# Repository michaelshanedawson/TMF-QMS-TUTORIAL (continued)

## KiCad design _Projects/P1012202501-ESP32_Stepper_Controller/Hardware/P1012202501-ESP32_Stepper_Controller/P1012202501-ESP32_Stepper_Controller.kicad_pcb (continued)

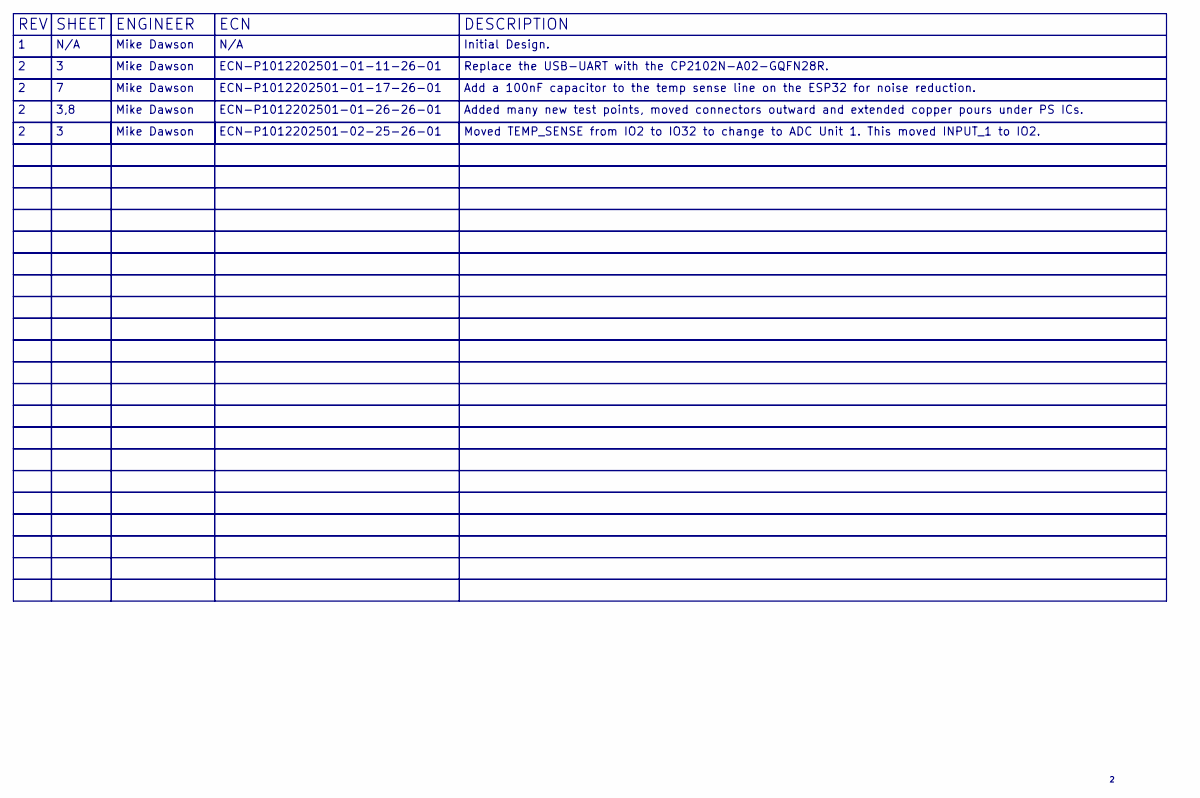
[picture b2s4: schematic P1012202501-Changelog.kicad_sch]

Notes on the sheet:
ECN
ECN-P1012202501-01-11-26-01
SHEET
DESCRIPTION
ECN-P1012202501-02-25-26-01
3,8
Mike Dawson
ECN-P1012202501-01-26-26-01
ECN-P1012202501-01-17-26-01
N/A
Replace the USB-UART with the CP2102N-A02-GQFN28R.
Initial Design.
REV
ENGINEER
Add a 100nF capacitor to the temp sense line on the ESP32 for noise reduction.
Added many new test points, moved connectors outward and extended copper pours under PS ICs.
Moved TEMP_SENSE from IO2 to IO32 to change to ADC Unit 1. This moved INPUT_1 to IO2.

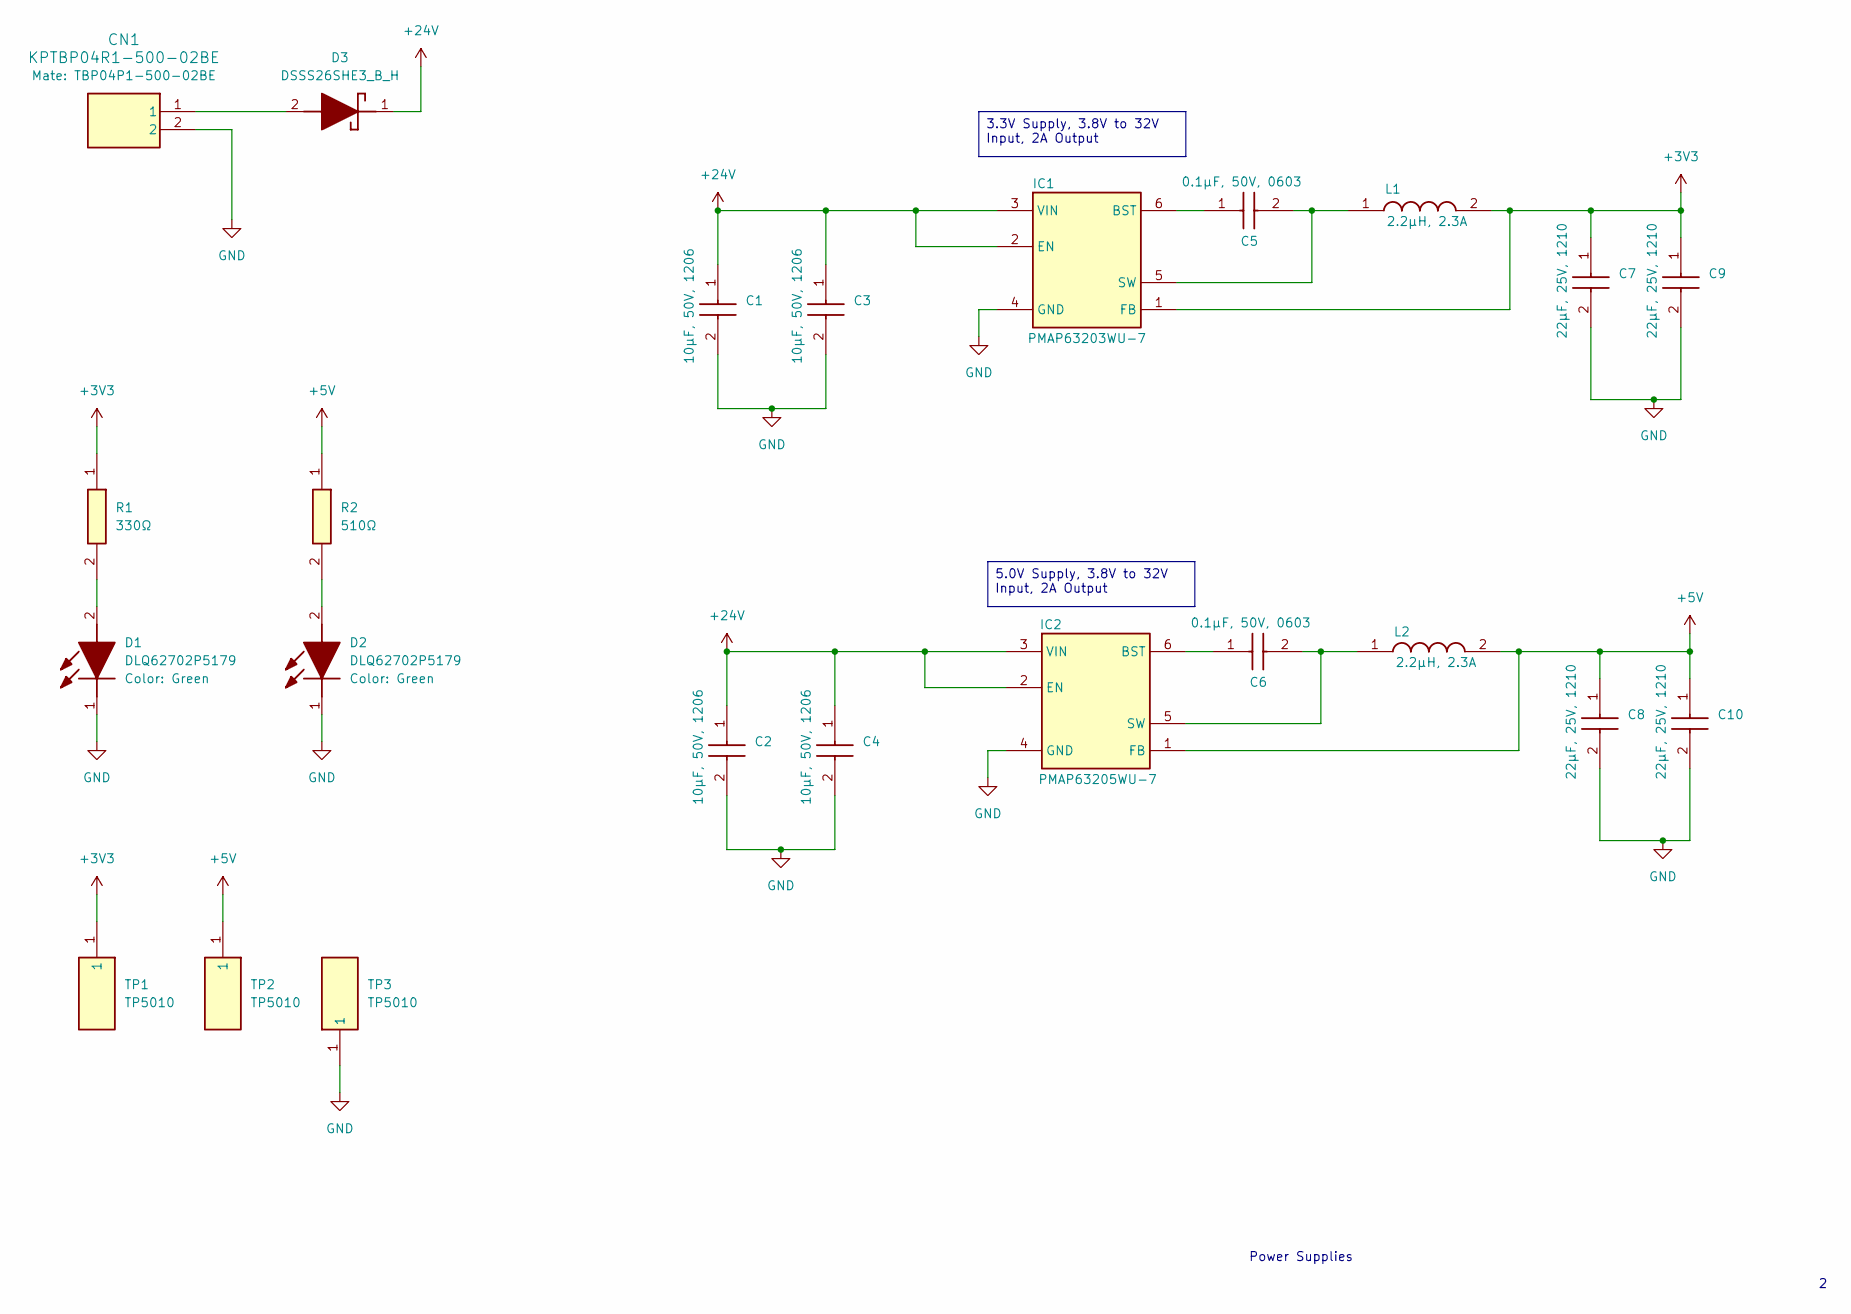
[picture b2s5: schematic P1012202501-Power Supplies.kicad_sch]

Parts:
C1, C2, C3, C4: CC1206106050AAAX7R; CAP-1206
C5, C6: CC0603104050AAAX7R; CAP-0603
C7, C8, C9, C10: CC1210226025AAAX7R; CAP-1210
CN1: KPTBP04R1-500-02BE; TBP04R1-500-02BE
D1, D2: DLQ62702P5179; LED-0805
D3: DSSS26SHE3_B_H; SMA
IC1: PMAP63203WU-7; TSOT-26-6
IC2: PMAP63205WU-7; TSOT-26-6
L1, L2: LSRP2512-2R2M; IND-1005
R1: RC0603330075AAA; RES-0603
R2: RC0603510075AAA; RES-0603
TP1, TP2, TP3: TP5010; 5010

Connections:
+3V3: C7.1, C9.1, IC1.1 (FB), L1.2, R1.1, TP1.1; also elsewhere on the board
+5V: C8.1, C10.1, IC2.1 (FB), L2.2, R2.1, TP2.1; also elsewhere on the board
+24V: C1.1, C2.1, C3.1, C4.1, D3.1 (K), IC1.2 (EN), IC1.3 (VIN), IC2.2 (EN), IC2.3 (VIN); also elsewhere on the board
GND: C1.2, C2.2, C3.2, C4.2, C7.2, C8.2, C9.2, C10.2, CN1.2, D1.1 (K), D2.1 (K), IC1.4 (GND), IC2.4 (GND), TP3.1; also elsewhere on the board
unnamed: D1.2 (A), R1.2
unnamed: D2.2 (A), R2.2
unnamed: CN1.1, D3.2 (A)
unnamed: C5.1, IC1.6 (BST)
unnamed: C5.2, IC1.5 (SW), L1.1
unnamed: C6.1, IC2.6 (BST)
unnamed: C6.2, IC2.5 (SW), L2.1

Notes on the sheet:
Power Supplies
3.3V Supply, 3.8V to 32V Input, 2A Output
5.0V Supply, 3.8V to 32V Input, 2A Output

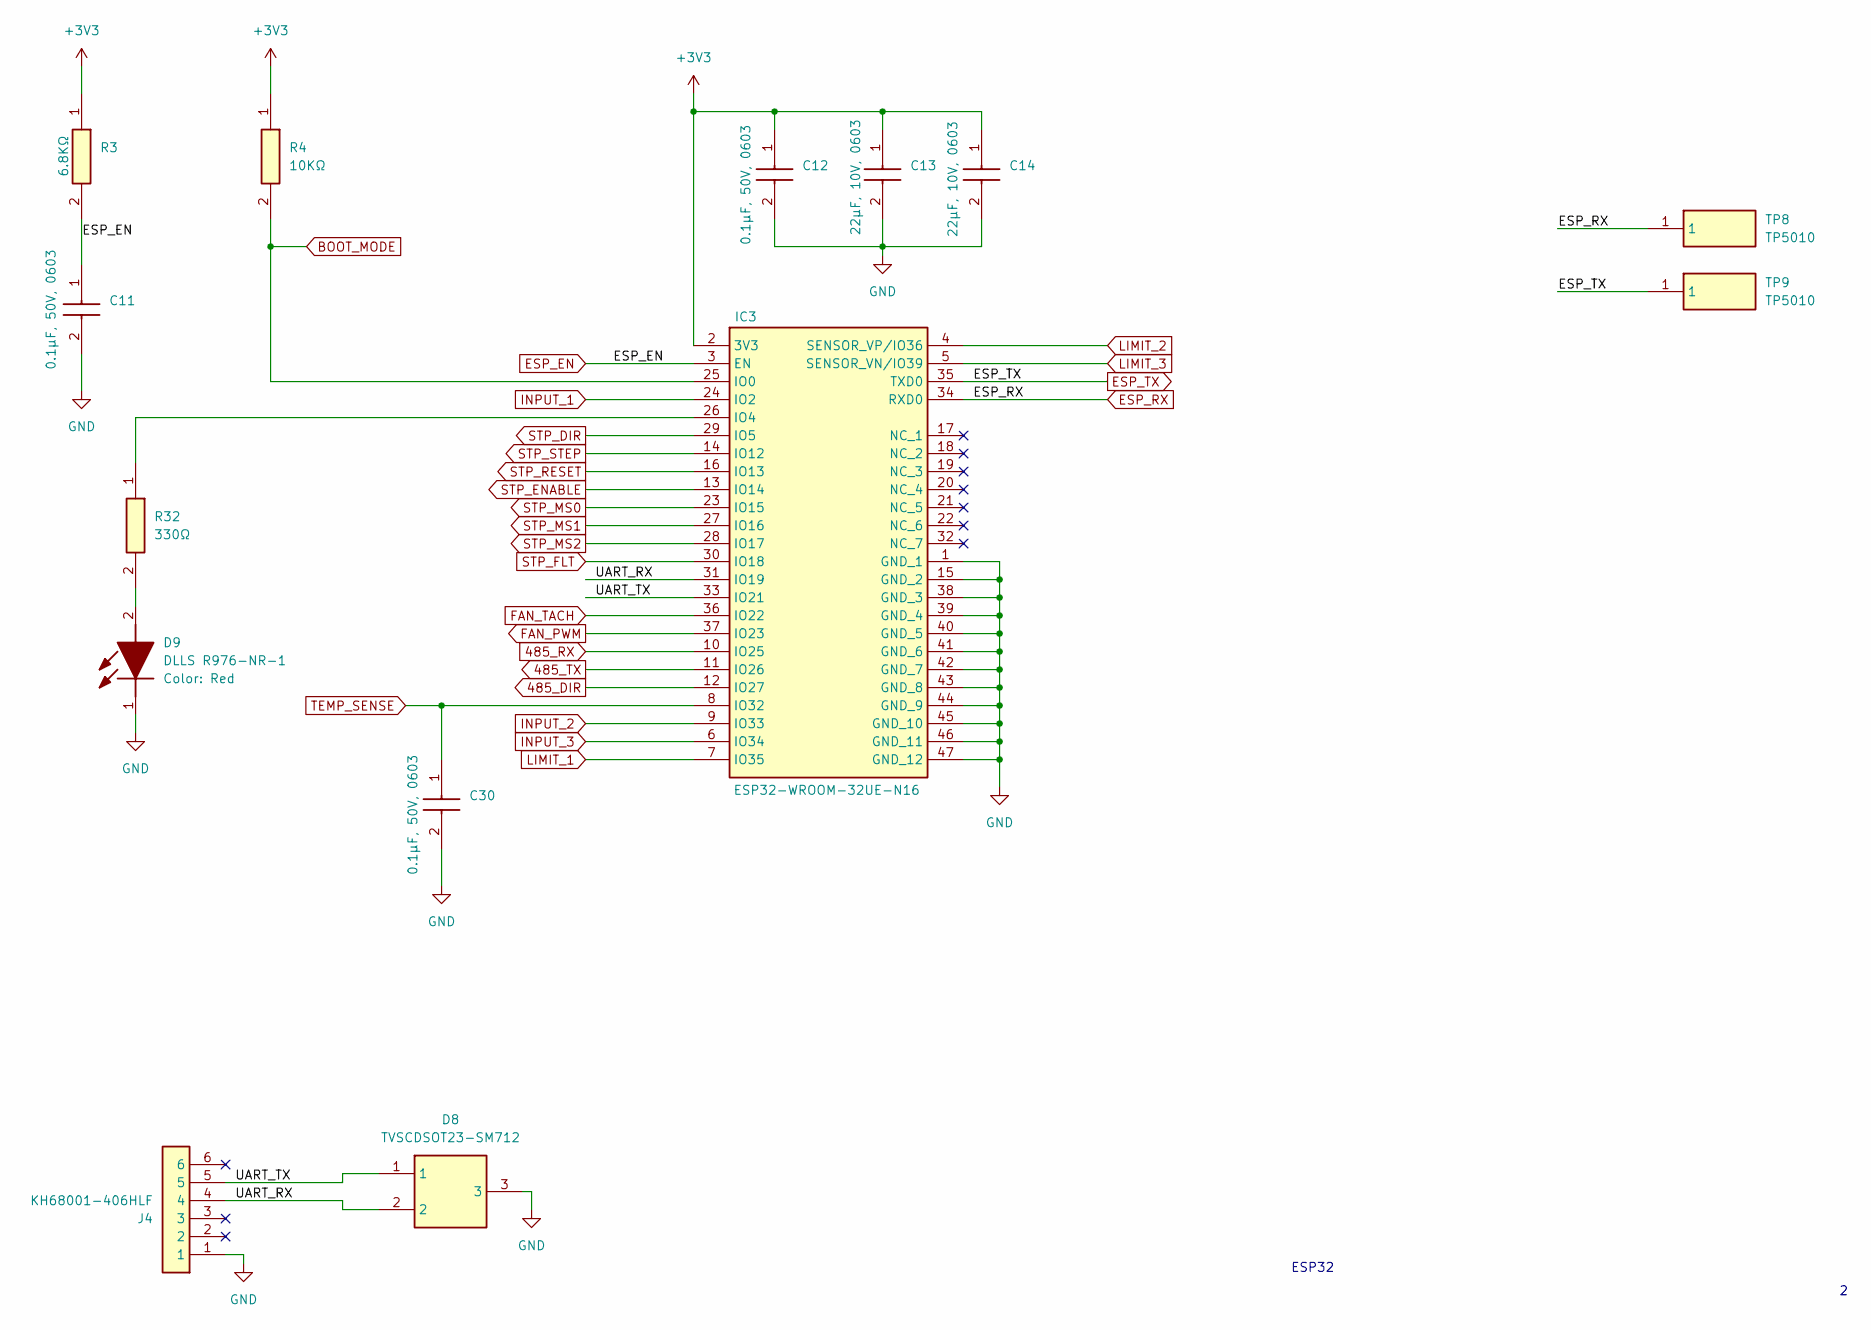
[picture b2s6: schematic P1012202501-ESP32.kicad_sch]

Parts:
C11, C12, C30: CC0603104050AAAX7R; CAP-0603
C13, C14: CC0603226010AABX5R; CAP-0603
D8: TVSCDSOT23-SM712; SOT-23-3
D9: DLLS R976-NR-1; LED-0805
IC3: ESP32-WROOM-32UE-N16; ESP32WROOM32UE
J4: KH68001-406HLF; 6x1HDR2.54mm
R3: RC0603682075AAA; RES-0603
R4: RC060310K2075AAA; RES-0603
R32: RC0603330075AAA; RES-0603
TP8, TP9: TP5010; 5010

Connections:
485_DIR: IC3.12 (IO27); also elsewhere on the board
485_RX: IC3.10 (IO25); also elsewhere on the board
485_TX: IC3.11 (IO26); also elsewhere on the board
+3V3: C12.1, C13.1, C14.1, IC3.2 (3V3), R3.1, R4.1; also elsewhere on the board
/ESP32/UART_RX: D8.2, IC3.31 (IO19), J4.4
/ESP32/UART_TX: D8.1, IC3.33 (IO21), J4.5
BOOT_MODE: IC3.25 (IO0), R4.2; also elsewhere on the board
ESP_EN: C11.1, IC3.3 (EN), R3.2; also elsewhere on the board
ESP_RX: IC3.34 (RXD0), TP8.1; also elsewhere on the board
ESP_TX: IC3.35 (TXD0), TP9.1; also elsewhere on the board
FAN_PWM: IC3.37 (IO23); also elsewhere on the board
FAN_TACH: IC3.36 (IO22); also elsewhere on the board
GND: C11.2, C12.2, C13.2, C14.2, C30.2, D8.3, D9.1 (K), IC3.1 (GND_1), IC3.15 (GND_2), IC3.38 (GND_3), IC3.39 (GND_4), IC3.40 (GND_5), IC3.41 (GND_6), IC3.42 (GND_7), IC3.43 (GND_8), IC3.44 (GND_9), IC3.45 (GND_10), IC3.46 (GND_11), IC3.47 (GND_12), J4.1; also elsewhere on the board
INPUT_1: IC3.24 (IO2); also elsewhere on the board
INPUT_2: IC3.9 (IO33); also elsewhere on the board
INPUT_3: IC3.6 (IO34); also elsewhere on the board
LIMIT_1: IC3.7 (IO35); also elsewhere on the board
LIMIT_2: IC3.4 (SENSOR_VP/IO36); also elsewhere on the board
LIMIT_3: IC3.5 (SENSOR_VN/IO39); also elsewhere on the board
unnamed: D9.2 (A), R32.2
unnamed: IC3.26 (IO4), R32.1
STP_DIR: IC3.29 (IO5); also elsewhere on the board
STP_ENABLE: IC3.13 (IO14); also elsewhere on the board
STP_FLT: IC3.30 (IO18); also elsewhere on the board
STP_MS0: IC3.23 (IO15); also elsewhere on the board
STP_MS1: IC3.27 (IO16); also elsewhere on the board
STP_MS2: IC3.28 (IO17); also elsewhere on the board
STP_RESET: IC3.16 (IO13); also elsewhere on the board
STP_STEP: IC3.14 (IO12); also elsewhere on the board
TEMP_SENSE: C30.1, IC3.8 (IO32); also elsewhere on the board

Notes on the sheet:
ESP32

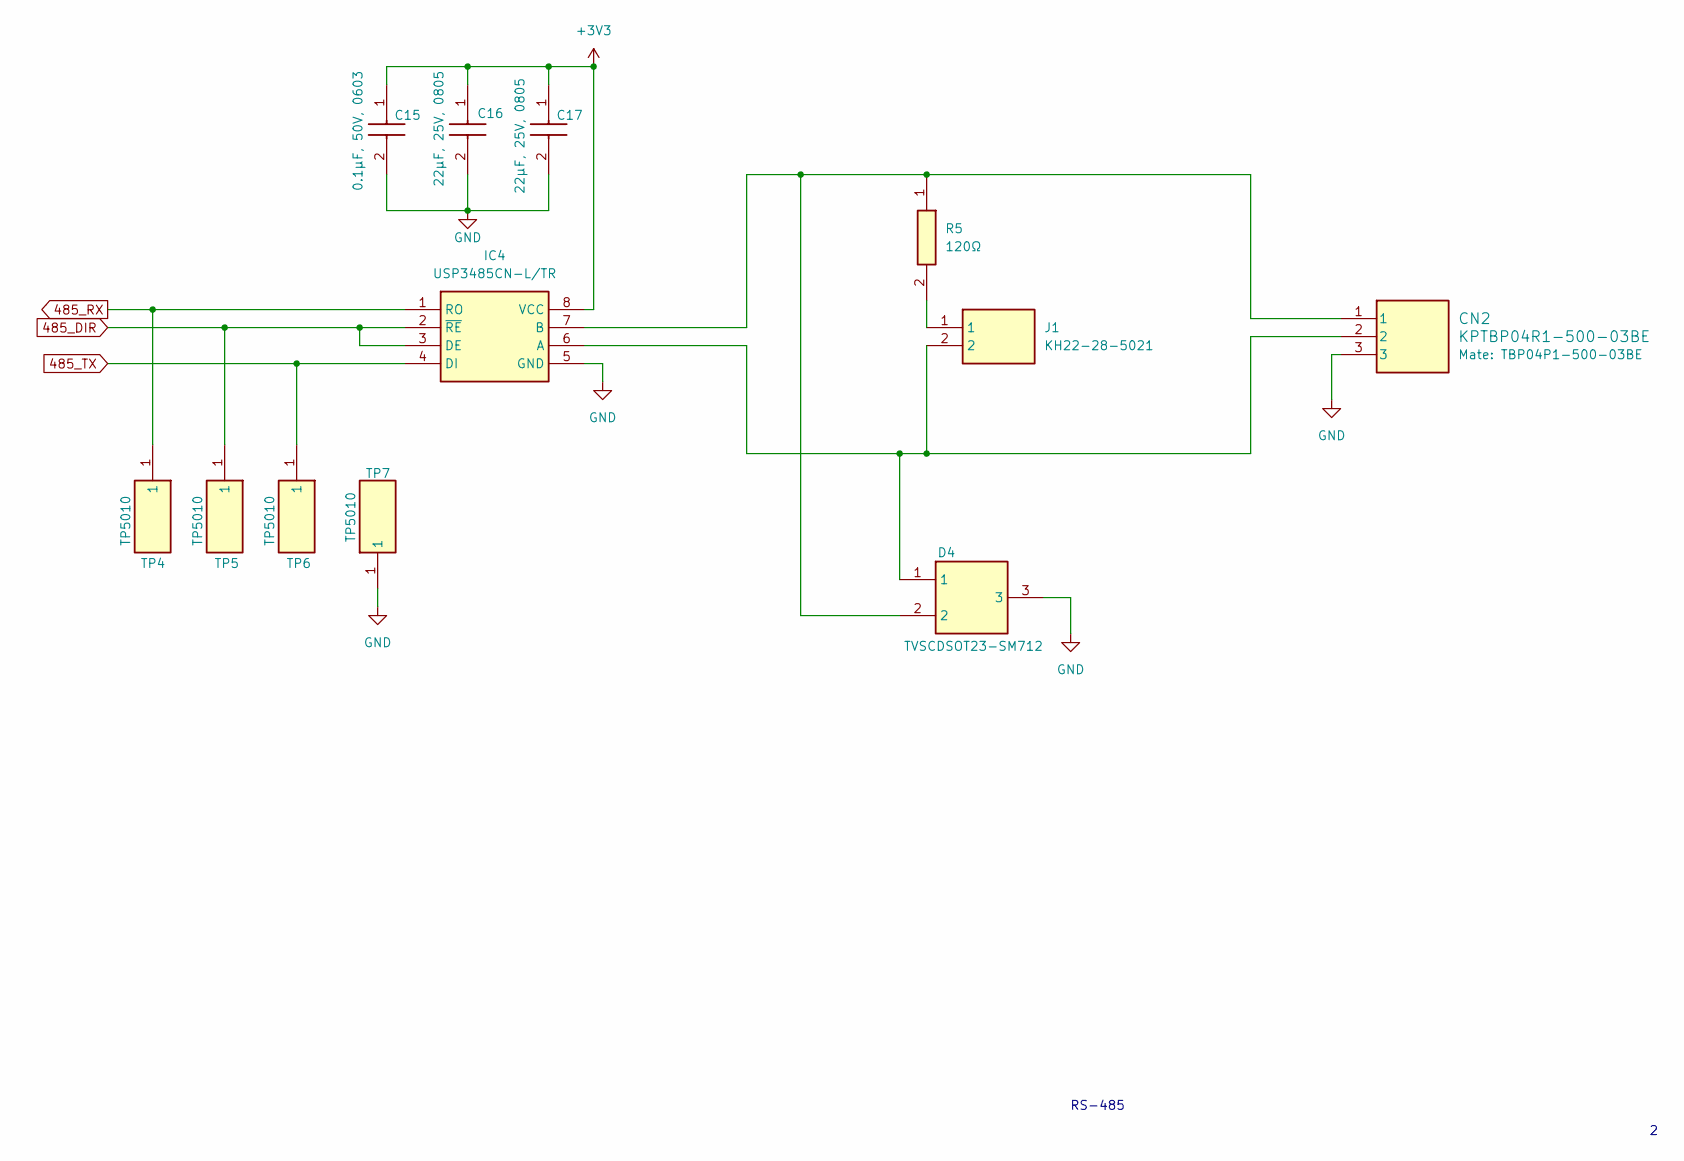
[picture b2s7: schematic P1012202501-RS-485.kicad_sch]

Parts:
C15: CC0603104050AAAX7R; CAP-0603
C16, C17: CC0805226025AABX5R; CAP-0805
CN2: KPTBP04R1-500-03BE; TBP04R1-500-03BE
D4: TVSCDSOT23-SM712; SOT-23-3
IC4: USP3485CN-L/TR; SOIC-8
J1: KH22-28-5021; 2x1HDR2.54mm
R5: RC0805121150AAB; RES-0805
TP4, TP5, TP6, TP7: TP5010; 5010

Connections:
485_DIR: IC4.2 (~RE), IC4.3 (DE), TP5.1; also elsewhere on the board
485_RX: IC4.1 (RO), TP4.1; also elsewhere on the board
485_TX: IC4.4 (DI), TP6.1; also elsewhere on the board
+3V3: C15.1, C16.1, C17.1, IC4.8 (VCC); also elsewhere on the board
GND: C15.2, C16.2, C17.2, CN2.3, D4.3, IC4.5 (GND), TP7.1; also elsewhere on the board
unnamed: CN2.2, D4.1, IC4.6 (A), J1.2
unnamed: CN2.1, D4.2, IC4.7 (B), R5.1
unnamed: J1.1, R5.2

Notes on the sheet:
RS-485

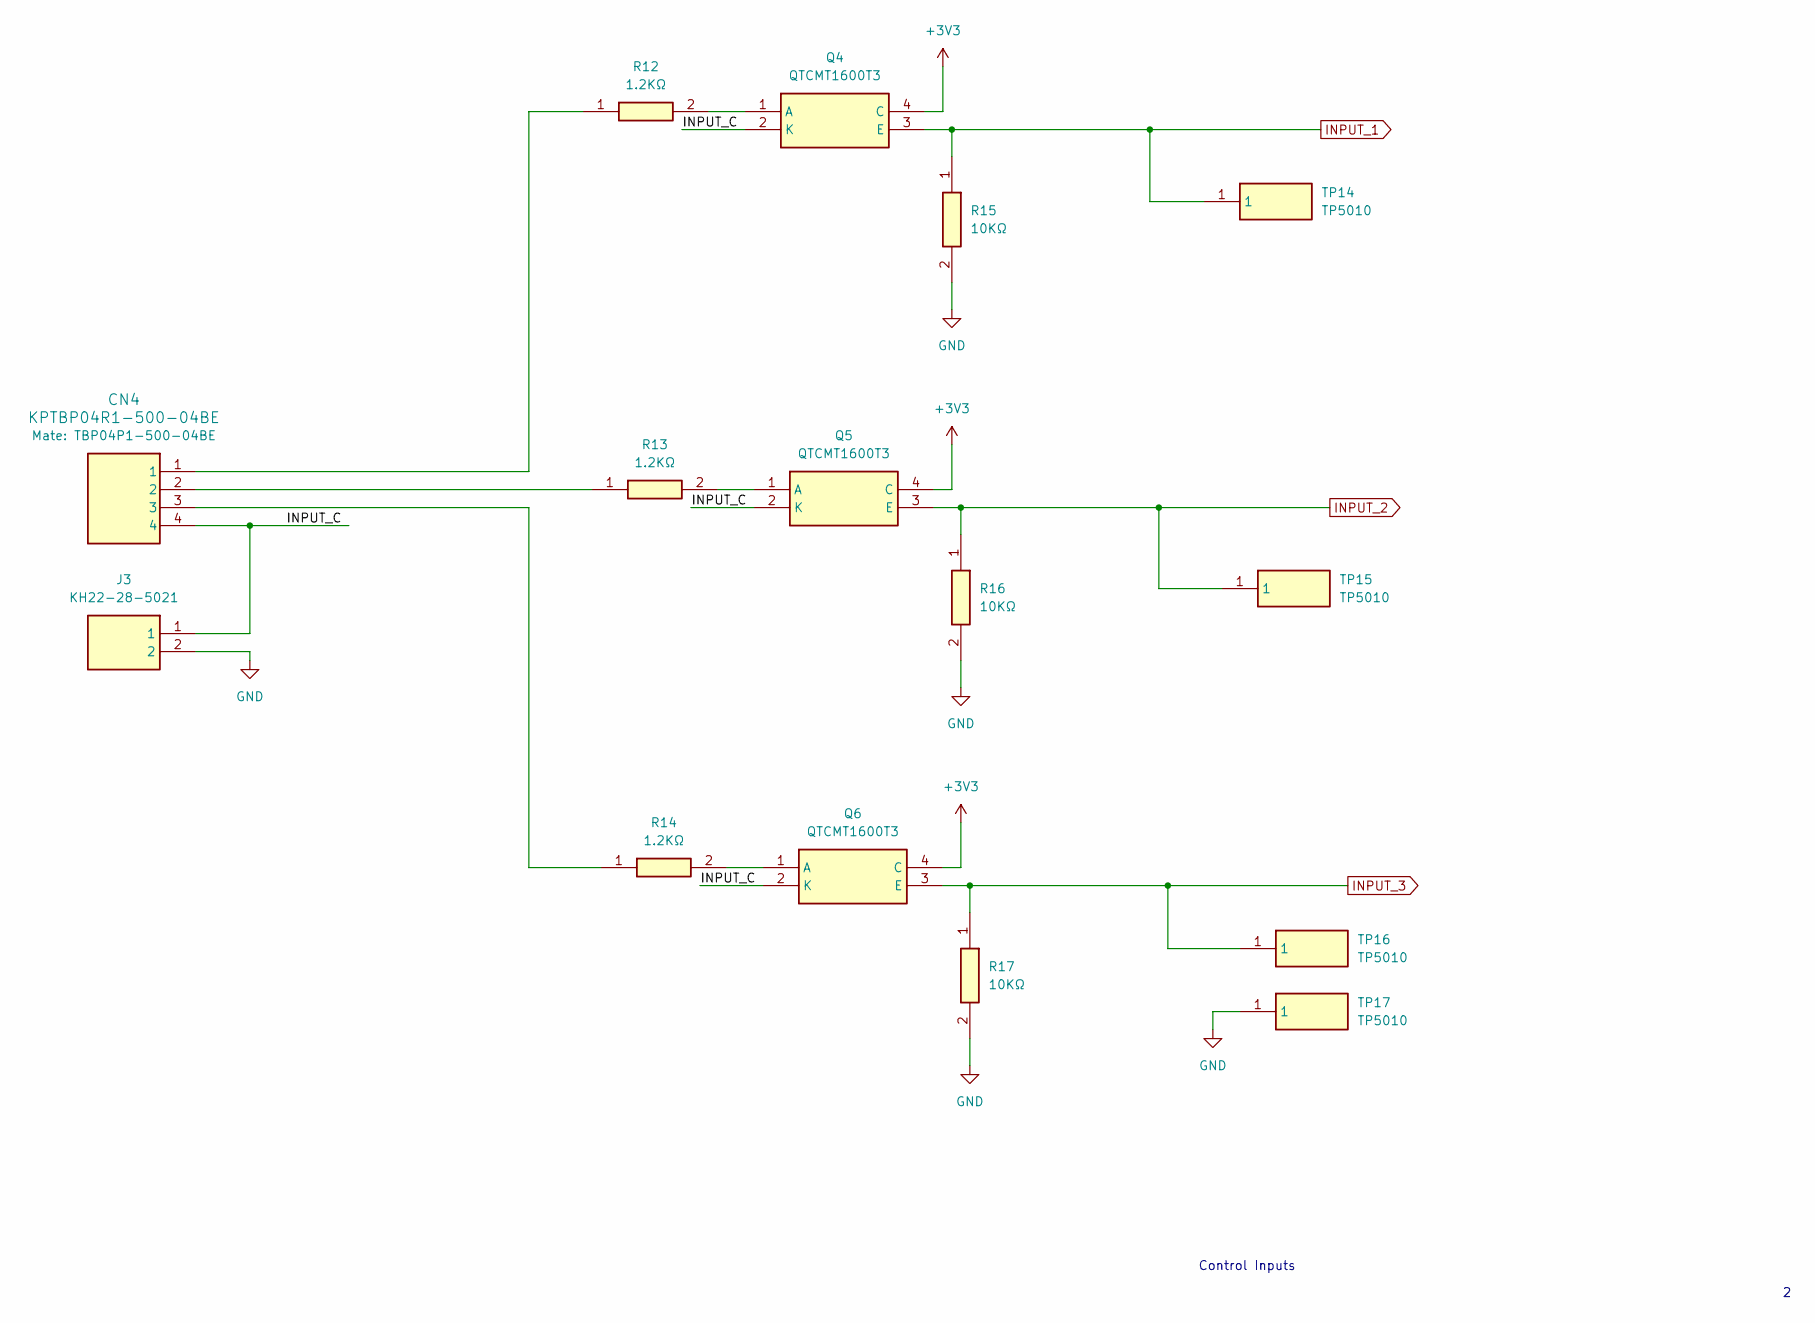
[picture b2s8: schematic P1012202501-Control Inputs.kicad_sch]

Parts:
CN4: KPTBP04R1-500-04BE; TBP04R1-500-04BE
J3: KH22-28-5021; 2x1HDR2.54mm
Q4, Q5, Q6: QTCMT1600T3; TCMT1600T3
R12, R13, R14: RC12101K2200AAC; RES-1210
R15, R16, R17: RC060310K2075AAA; RES-0603
TP14, TP15, TP16, TP17: TP5010; 5010

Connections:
+3V3: Q4.4 (C), Q5.4 (C), Q6.4 (C); also elsewhere on the board
/Control Inputs/INPUT_C: CN4.4, J3.1, Q4.2 (K), Q5.2 (K), Q6.2 (K)
GND: J3.2, R15.2, R16.2, R17.2, TP17.1; also elsewhere on the board
INPUT_1: Q4.3 (E), R15.1, TP14.1; also elsewhere on the board
INPUT_2: Q5.3 (E), R16.1, TP15.1; also elsewhere on the board
INPUT_3: Q6.3 (E), R17.1, TP16.1; also elsewhere on the board
unnamed: CN4.1, R12.1
unnamed: CN4.2, R13.1
unnamed: CN4.3, R14.1
unnamed: Q4.1 (A), R12.2
unnamed: Q5.1 (A), R13.2
unnamed: Q6.1 (A), R14.2

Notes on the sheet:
Control Inputs

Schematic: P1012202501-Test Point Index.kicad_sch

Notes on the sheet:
Test Point Index
TP30 - STP_STEP TP31 - STP_MS0 TP32 - STP_MS1 TP33 - STP_MS2 TP34 - STP_FLT TP35 - FAN_TACH TP36 - FAN_PWM
TP1 - 3.3v TP2 - 5v TP3 - GND TP4 - 485_RX TP5 - 485_DIR TP6 - 485_TX TP7 - GND TP8 - ESP_RX TP9 - ESP_TX TP10 - LIMIT_1 TP11 - LIMIT_2 TP12 - LIMIT_3 TP13 - GND TP14 - INPUT_1 TP15 - INPUT_2 TP16 - INPUT_3 TP17 - GND TP18 - RTS TP19 - DTR TP20 - BOOT_MODE TP21 - ESP_EN TP22 - USB_D_P TP23 - USB_D_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

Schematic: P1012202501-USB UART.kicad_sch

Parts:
C18, C20: CC0603104050AAAX7R; CAP-0603
C19, C21: CC0603226010AABX5R; CAP-0603
CN5: KUSB4105-GF-A; GCT_USB4105-GF-A
D5, D6, D7: TVSCDSOT23-SM712; SOT-23-3
IC5: UCP2102C-A01-GQFN28; QFN-28
Q7: QBC847BDW1T1G; SC-70-6
R18: RC060322K1075AAA; RES-0603
R19: RC060347K5075AAA; RES-0603
R20, R21: RC060310K2075AAA; RES-0603
R22: RC06031K0075AAA; RES-0603
S1, S2: SW435151014845; 435151014845
TP18, TP19, TP20, TP21, TP22, TP23, TP24, TP25: TP5010; 5010

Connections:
+3V3: C20.1, C21.1, IC5.6 (VDD), IC5.7 (VREGIN), R22.1; also elsewhere on the board
/USB UART/DTR: IC5.28 (DTR), Q7.1 (E2), R21.1, TP19.1
/USB UART/RTS: IC5.24 (RTS), Q7.4 (E1), R20.2, TP18.1
/USB UART/USB_D_N: CN5.A7 (DN1), CN5.B7 (DN2), D5.2, IC5.5 (D-), TP23.1
/USB UART/USB_D_P: CN5.A6 (DP1), CN5.B6 (DP2), D5.1, IC5.4 (D+), TP22.1
BOOT_MODE: D7.1, Q7.6 (C2), S1.3 (COM_1), S1.4 (COM_2), TP20.1; also elsewhere on the board
ESP_EN: D7.2, Q7.3 (C1), S2.3 (COM_1), S2.4 (COM_2), TP21.1; also elsewhere on the board
ESP_RX: IC5.26 (TXD); also elsewhere on the board
ESP_TX: IC5.25 (RXD); also elsewhere on the board
GND: C18.2, C19.2, C20.2, C21.2, CN5.A1_B12 (GND), CN5.B1_A12 (GND__1), CN5.SH1 (SHELL_GND), CN5.SH2 (SHELL_GND__1), CN5.SH3 (SHELL_GND__2), CN5.SH4 (SHELL_GND__3), D5.3, D6.3, D7.3, IC5.3 (GND_1), IC5.29 (GND_2), R19.2, S1.1 (NO_1), S1.2 (NO_2), S1.5 (GND_1), S1.6 (GND_2), S2.1 (NO_1), S2.2 (NO_2), S2.5 (GND_1), S2.6 (GND_2), TP25.1; also elsewhere on the board
unnamed: IC5.9 (RSTB), R22.2
unnamed: C18.1, C19.1, IC5.8 (VBUS), R18.2, R19.1
unnamed: Q7.5 (B1), R21.2
unnamed: Q7.2 (B2), R20.1
VBUS: CN5.A4_B9 (VBUS), CN5.B4_A9 (VBUS__1), D6.1, R18.1, TP24.1

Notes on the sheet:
USB UART
AUTOPROGRAM DTR RTS : EN BOOT 1 1 : 1 1 0 0 : 1 1 1 0 : 0 1 0 1 : 1 0

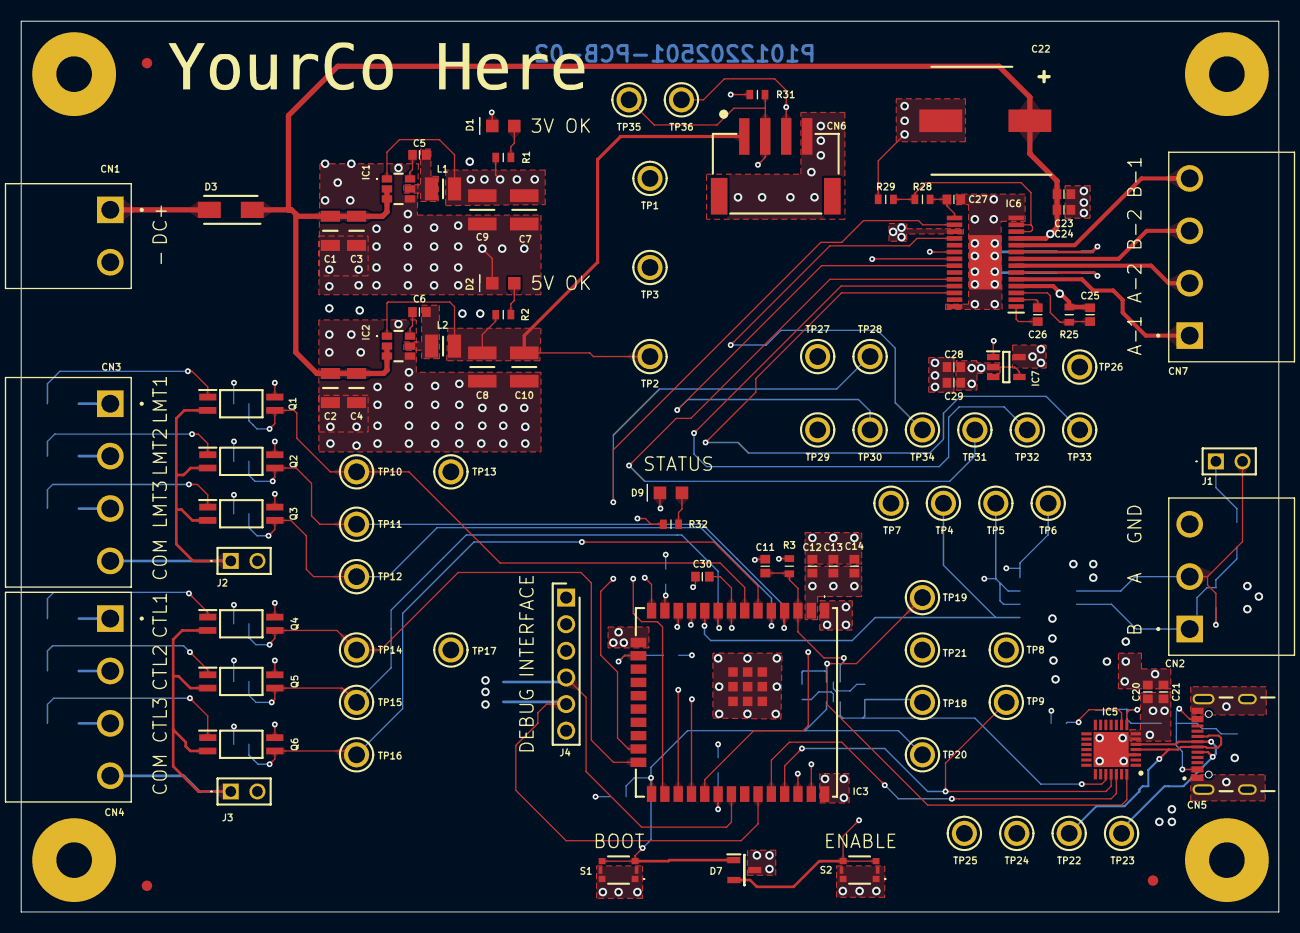
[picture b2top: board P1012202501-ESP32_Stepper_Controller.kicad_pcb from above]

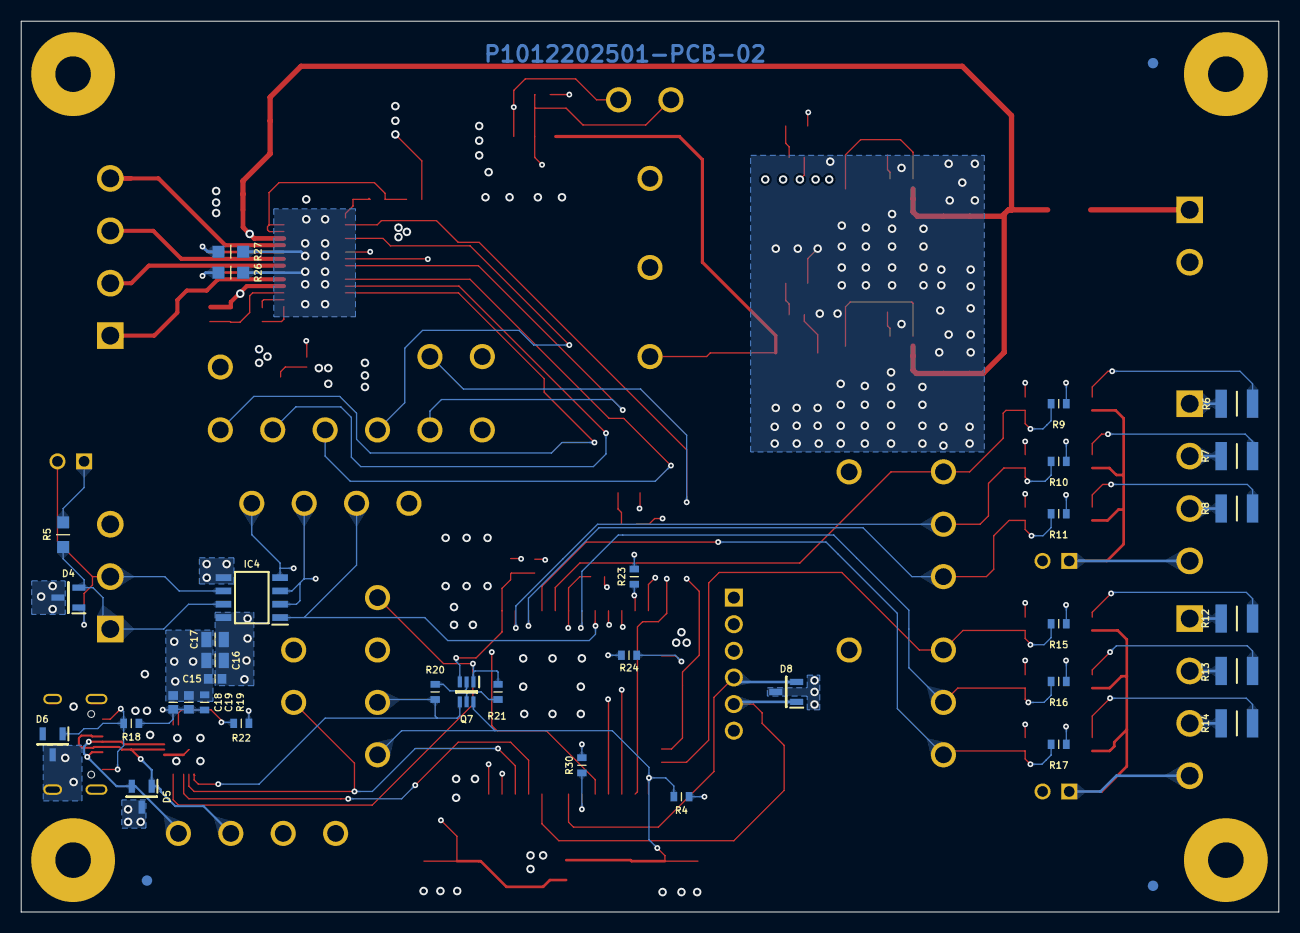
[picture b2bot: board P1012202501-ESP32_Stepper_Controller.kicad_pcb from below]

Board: 6 copper layers, 120.0 x 85.0 mm, 147 parts (38 on the bottom side), 76 nets.

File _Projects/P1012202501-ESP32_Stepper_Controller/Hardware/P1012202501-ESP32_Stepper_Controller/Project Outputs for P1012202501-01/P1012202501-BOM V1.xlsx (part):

Project: |  | P1012202501-01 |  |  |  |  | Per board LV Cost | 78.489999999999995 | Per board HV Cost | 26.269000000000005
BOM Version: |  | 1
Reference | Qty | Internal Part Number | Manufacturer 1 | Manufacturer 1 P/N | Vendor 1a | Vendor 1a P/N | Vendor 1a Cost LV | Vendor 1a LV Extended | Vendor 1a Cost HV | Vendor 1a HV Extended | Vendor 1b | Vendor 1b P/N | Vendor 1b Cost HV | Vendor 1b Cost LV | Notes
C1,C2,C3,C4 | 4 | CC1206106050AAAX7R | Samsung | CL31B106KBHNNNE | Mouser | 187-CL31B106KBHNNNE | 0.22 | 0.88 | 6.8000000000000005E-2 | 0.27200000000000002
C5,C6,C11,C12,C15,C18,C20,C23,C24,C25,C28 | 11 | CC0603104050AAAX7R | Yageo | CC0603KRX7R9BB104 | Mouser | 603-CC603KRX7R9BB104 | 0.1 | 1.1000000000000001 | 1.2E-2 | 0.13200000000000001
C7,C8,C9,C10 | 4 | CC1210226025AAAX7R | Taiyo Yuden | TMK325B7226KM-PR | Mouser | 963-TMK325B7226KM-PR | 0.6 | 2.4 | 0.187 | 0.748
C13,C14,C19,C21,C29 | 5 | CC0603226010AABX5R | Murata | GRM188R61A226ME15D | Mouser | 81-GRM188R61A226ME5D | 0.1 | 0.5 | 2.3E-2 | 0.11499999999999999
C16,C17 | 2 | CC0805226025AABX5R | Samsung | CL21A226MAYNNNE | Mouser | 187-CL21A226MAYNNNE | 0.1 | 0.2 | 4.2999999999999997E-2 | 8.5999999999999993E-2
C22 | 1 | CEA771MS107M1JLAS018 | KEMET | A771MS107M1JLAS018 | Mouser | 80-A771MS107M1JLAS18 | 1.49 | 1.49 | 0.47199999999999998 | 0.47199999999999998
C26 | 1 | CC0603103050AAAX7R | Murata | GCM188R71H103KA37J | Mouser | 81-GCM188R71H103KA7J | 0.1 | 0.1 | 1.9E-2 | 1.9E-2
C27 | 1 | CC0603474050AAAX7R | TAIYO YUDEN | UMK107B7474KA-TR | Mouser | 963-UMK107B7474KA-TR | 0.15 | 0.15 | 3.5000000000000003E-2 | 3.5000000000000003E-2
CN1 | 1 | KPTBP04R1-500-02BE | Same Sky | TBP04R1-500-02BE | Mouser | 179-TBP04R1-500-02BE | 0.33 | 0.33 | 0.128 | 0.128
CN2 | 1 | KPTBP04R1-500-03BE | Same Sky | TBP04R1-500-03BE | Mouser | 179-TBP04R1-500-03BE | 0.48 | 0.48 | 0.189 | 0.189
CN3,CN4,CN7 | 3 | KPTBP04R1-500-04BE | Same Sky | TBP04R1-500-04BE | Mouser | 179-TBP04R1-500-04BE | 0.62 | 1.8599999999999999 | 0.246 | 0.73799999999999999
CN5 | 1 | KUSB4105-GF-A | GCT | USB4105-GF-A | Mouser | 640-USB4105-GF-A | 0.78 | 0.78 | 0.48399999999999999 | 0.48399999999999999
CN6 | 1 | KHS4B-PH-SM4-TB(LF)(SN) | JST | S4B-PH-SM4-TB(LF)(SN) | Mouser | 306-S4BPHSM4TBLFSN | 0.79 | 0.79 | 0.36899999999999999 | 0.36899999999999999
D1,D2 | 2 | DLQ62702P5179 | OSRAM | Q62702P5179 | Mouser | 720-Q62702P5179 | 0.27 | 0.54 | 4.9000000000000002E-2 | 9.8000000000000004E-2
D3 | 1 | DSSS26SHE3_B_H | Vishay | SS26SHE3_B/H | Mouser | 78-SS26SHE3_B/H | 0.36 | 0.36 | 7.5999999999999998E-2 | 7.5999999999999998E-2
D4,D5,D6,D7,D8 | 5 | TVSCDSOT23-SM712 | Bourns | CDSOT23-SM712 | Mouser | 652-CDSOT23-SM712 | 1.1100000000000001 | 5.5500000000000007 | 0.34300000000000003 | 1.7150000000000001
D9 | 1 | DLLS R976-NR-1 | OSRAM | LS R976-NR-1 | Mouser | 720-LSR976-NR-1 | 0.15 | 0.15 | 4.4999999999999998E-2 | 4.4999999999999998E-2
IC1 | 1 | PMAP63203WU-7 | Diodes Incorporated | AP63203WU-7 | Mouser | 621-AP63203WU-7 | 0.71 | 0.71 | 0.34200000000000003 | 0.34200000000000003
IC2 | 1 | PMAP63205WU-7 | Diodes Incorporated | AP63205WU-7 | Mouser | 621-AP63205WU-7 | 0.71 | 0.71 | 0.34200000000000003 | 0.34200000000000003
IC3 | 1 | ESP32-WROOM-32UE-N16 | Espressif | ESP32-WROOM-32UE-N16 | Mouser | 356-ESP32WRM32UE28UH | 6.71 | 6.71 | 3.98 | 3.98
IC4 | 1 | USP3485CN-L/TR | MaxLinear | SP3485CN-L/TR | Mouser | 701-SP3485CN-L/TR | 0.81 | 0.81 | 0.38 | 0.38 | DigiKey | 1016-1816-1-ND | 0.39506999999999998 | 0.81
IC5 | 1 | UCP2102C-A01-GQFN28 | Silicon Labs | CP2102C-A01-GQFN28 | Mouser | 634-P2102CA01GQFN28 | 3.55 | 3.55 | 1.31 | 1.31
IC6 | 1 | UDRV8825PWPR | Texas Instruments | DRV8825PWPR | Mouser | 595-DRV8825PWPR | 4.03 | 4.03 | 2.4 | 2.4
IC7 | 1 | UTMP36GRTZ-REEL7 | Analog Devices | TMP36GRTZ-REEL7 | Mouser | 584-TMP36GRTZ-R7 | 1.89 | 1.89 | 1.22 | 1.22
J1,J2,J3 | 3 | KH22-28-5021 | Molex | 22-28-5021 | Mouser | 538-22-28-5021 | 0.1 | 0.30000000000000004 | 7.0999999999999994E-2 | 0.21299999999999997
J4 | 1 | KH68001-406HLF | Amphenol | 68001-406HLF | Mouser | 649-68001-406HLF | 0.17 | 0.17 | 0.16300000000000001 | 0.16300000000000001
L1,L2 | 2 | LSRP2512-2R2M | Bourns | SRP2512-2R2M | Mouser | 652-SRP2512-2R2M | 0.33 | 0.66 | 0.19900000000000001 | 0.39800000000000002
Q1,Q2,Q3,Q4,Q5,Q6 | 6 | QTCMT1600T3 | Vishay Semiconductors | TCMT1600T3 | Mouser | 78-TCMT1600T3 | 0.76 | 4.5600000000000005 | 0.30299999999999999 | 1.8180000000000001
Q7 | 1 | QBC847BDW1T1G | onsemi | BC847BDW1T1G | Mouser | 863-BC847BDW1T1G | 0.14000000000000001 | 0.14000000000000001 | 0.42 | 0.42
R1,R32 | 2 | RC0603330075AAA | Yageo | RT0603FRE13330RL | Mouser | 603-RT0603FRE13330RL | 0.19 | 0.38 | 1.4999999999999999E-2 | 0.03
R2 | 1 | RC0603510075AAA | Yageo | SR0603FR-7W510RL | Mouser | 603-SR0603FR-7W510RL | 0.1 | 0.1 | 2.1000000000000001E-2 | 2.1000000000000001E-2
R3 | 1 | RC0603682075AAA | Panasonic | ERA-3AEB682V | Mouser | 667-ERA-3AEB682V | 0.1 | 0.1 | 4.2999999999999997E-2 | 4.2999999999999997E-2
R4,R20,R21,R23,R24,R30,R9,R10,R11,R15,R16,R17 | 12 | RC060310K2075AAA | Yageo | AC0603DRE0710KL | Mouser | 603-AC0603DRE0710KL | 0.11 | 1.32 | 3.1E-2 | 0.372
R5 | 1 | RC0805121150AAB | Panasonic | ERJ-6GEYJ121V | Mouser | 667-ERJ-6GEYJ121V | 0.1 | 0.1 | 1.2999999999999999E-2 | 1.2999999999999999E-2
R6,R7,R8,R12,R13,R14 | 6 | RC12101K2200AAC | Yageo | AC1210JR-071K2L | Mouser | 603-AC1210JR-071K2L | 0.12 | 0.72 | 4.1000000000000002E-2 | 0.246
R18 | 1 | RC060322K1075AAA | Vishay | CRCW060322K1FKEBC | Mouser | 71-CRCW060322K1FKEBC | 0.11 | 0.11 | 8.9999999999999993E-3 | 8.9999999999999993E-3
R19 | 1 | RC060347K5075AAA | Panasonic | ERA-3AEB4752V | Mouser | 667-ERA-3AEB4752V | 0.1 | 0.1 | 4.2000000000000003E-2 | 4.2000000000000003E-2
R22,R31 | 2 | RC06031K0075AAA | Yageo | SR0603JR-071KL | Mouser | 603-SR0603JR-071KL | 0.11 | 0.22 | 3.1E-2 | 6.2E-2
R25 | 1 | RC06031M0075AAA | Vishay | MCT0603MD1004BP500 | Mouser | 594-MCT0603MD1004BP5 | 0.24 | 0.24 | 0.13900000000000001 | 0.13900000000000001
R26,R27 | 2 | RC08050R2075AAE | Vishay | RCWE0805R200FKEA | Mouser | 71-RCWE0805R200FKEA | 0.17 | 0.34 | 5.0999999999999997E-2 | 0.10199999999999999
R28 | 1 | RC060350K075AAA | Yageo | RT0603BRD0750KL | Mouser | 603-RT0603BRD0750KL | 0.14000000000000001 | 0.14000000000000001 | 5.1999999999999998E-2 | 5.1999999999999998E-2
R29 | 1 | RC060330K075AAA | Panasonic | ERA-3AED303V | Mouser | 667-ERA-3AED303V | 0.17 | 0.17 | 4.8000000000000001E-2 | 4.8000000000000001E-2
S1,S2 | 2 | SW435151014845 | Wurth Elektronik | 435151014845 | Mouser | 710-435151014845 | 0.54 | 1.08 | 0.36299999999999999 | 0.72599999999999998
TP1,TP2,TP3,TP4,TP5,TP6,TP7,TP10,TP11,TP12,TP13,TP14,TP15,TP16,TP17,TP18,TP19,T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 | 23 | TP5010 | Keystone | 5010 | Mouser | 534-5010 | 0.33 | 7.5900000000000007 | 0.188 | 4.3239999999999998
PCB | 1 | P1012202501-PCB-01 |  |  |  |  | 5 | 5 | 1 | 1
Jumper for J1, J2, and J3 | 3 | JMP2POS1ROW254 | JST | JM-2BK-61 | Mouser | 306-JM-2BK-61 | 0.23 | 0.69000000000000006 | 0.111 | 0.33300000000000002
Plug for CN1 | 1 | KPTBP04P1-500-02BE | Same Sky | TBP04P1-500-02BE | Mouser | 179-TBP04P1-500-02BE | 0.76 | 0.76 |  | 0
Plug for CN2 | 1 | KPTBP04P1-500-03BE | Same Sky | TBP04P1-500-03BE | Mouser | 179-TBP04P1-500-03BE | 1.06 | 1.06 |  | 0
Plug for CN3, CN4, and CN7 | 3 | KPTBP04P1-500-04BE | Same Sky | TBP04P1-500-04BE | Mouser | 179-TBP04P1-500-04BE | 1.38 | 4.1399999999999997 |  | 0
Plug for CN6 | 1 | KPPHR-4 | JST | PHR-4 | Mouser | 306-PHR-4 | 0.1 | 0.1 |  | 0
Terminals for CN6 Plug | 4 | PTSPH-002T-P0.5L | JST | SPH-002T-P0.5L | Mouser | 306-SPH-002T-P0.5L | 0.13 | 0.52 |  | 0
Fan 1 | 1 | FANDC5V4040mmPWMTACH | Same Sky | CFM-4010-03-22 | Mouser | 490-CFM-4010-03-22 | 10.63 | 10.63 |  | 0
Heat Sink for IC6 | 1 | HS8.8x8.5x8 | Same Sky | HSB01-080808 | DigiKey | 2223-HSB01-080808-ND | 0.76 | 0.76 | 0.54100000000000004 | 0.54100000000000004
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
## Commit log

2025-11-01 Added new content.
2025-11-01 Removed lock file.
2025-11-05 Updating for latest stream.
2025-11-07 Adding all updated files from latest stream.
2025-11-08 Pushing updated content.
2025-11-11 Added content from latest stream.
2025-11-13 Added new content from stream.
2025-11-15 Adding new content from stream.
2025-11-15 Adding content from latest stream.
2025-11-20 Added new content from recent stream.
2025-11-25 Adding new materials from stream.
2025-11-27 Added new items from stream.
2025-11-29 Added new content and changes from stream.
2025-11-29 Added new content from the stream.
2025-11-30 Added items from latest stream.
2025-12-02 Added updated items from recent stream.
2025-12-06 Added new content from latest stream.
2025-12-06 Added latest content from stream.
2025-12-14 Added new items from recent stream.
2025-12-16 Added new content from stream, removed extra files.
2025-12-26 Added new content from stream the other day.
2025-12-27 Added recent files from stream.
2025-12-27 New content from latest stream.
2026-01-03 Added new files from stream.
2026-01-08 Pushing updated files from streams.
2026-01-19 Adding content from stream.
2026-01-29 Added new items from streams.
2026-02-28 Adding new items from recent streams.
2026-03-05 Adding new items from recent stream.
2026-03-30 Added updated content that I keep forgetting to do.
2026-05-24 Updated files from video stream.
